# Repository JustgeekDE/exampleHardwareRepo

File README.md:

# exampleHardwareRepo
This is a simple example project to try out [scoville](https://github.com/JustgeekDE/scoville).

The example projects can be found in the 'hardware' repository, the tests in 'test'. To run the tests you can use `./runTests simulationTests` for the simulation and `./runTests hardwareTests` to test against acutal hardware implementations.

The tests are executed in a virtual environment and use the latest version of scoville from the git master.

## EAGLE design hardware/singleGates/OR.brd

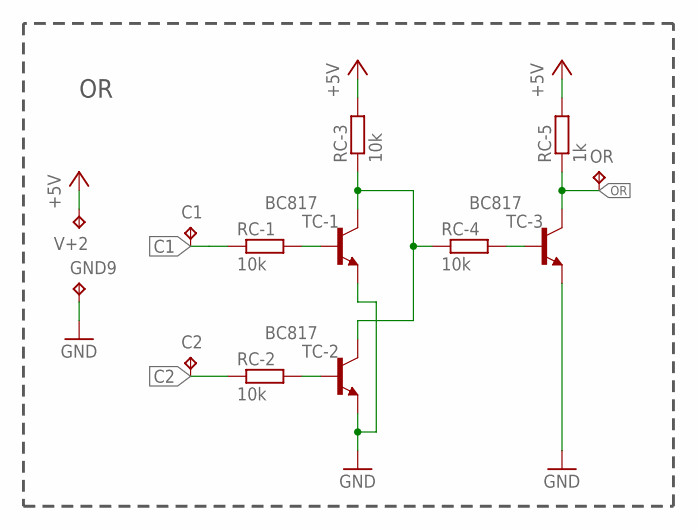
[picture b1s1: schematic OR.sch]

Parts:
C1, C2: TPTP07R; TP07R
GND9: TPTP07R; TP07R
OR: TPTP07R; TP07R
RC-1, RC-2, RC-3, RC-4: 10k; R0603
RC-5: 1k; R0603
TC-1, TC-2, TC-3: BC817; SOT23-BEC
V+2: TPTP07R; TP07R

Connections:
+5V: RC-3.2, RC-5.2, V+2.TP
C1: C1.TP, RC-1.1
C2: C2.TP, RC-2.1
GND: GND9.TP, TC-1.E, TC-2.E, TC-3.E
unnamed: RC-1.2, TC-1.B
unnamed: RC-2.2, TC-2.B
unnamed: RC-4.2, TC-3.B
unnamed: RC-3.1, RC-4.1, TC-1.C, TC-2.C
OR: OR.TP, RC-5.1, TC-3.C

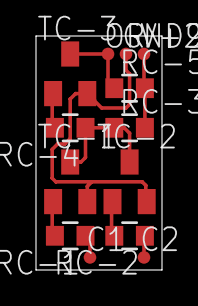
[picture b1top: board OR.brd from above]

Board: 2 copper layers, 7.0 x 13.0 mm, 13 parts (0 on the bottom side), 9 nets.

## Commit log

2016-01-20 Initial hardware files
2016-01-20 Board files are just confusing at the moment
2016-01-20 first tests
2016-01-21 Fixed tests
2016-01-21 Ignoring python files and idea
2016-01-21 Changed test filename to be py.test compatible
2016-01-21 changed timing tests
2016-02-02 Added XOR example
2016-02-08 Cleaning up tests, to make it possible to run the same tests against simulation and real hardware
2016-02-08 refactored hardware tests to reuse simulation tests
2016-02-08 run tests in virtual environment with auto checkout of scoville
2016-02-08 scripts to automatically run tests
2016-02-08 cleaning up test script
2016-02-08 Cleaned up test requirements, no need to always update pip and setup tools
2016-02-08 basic handler to run ERC
